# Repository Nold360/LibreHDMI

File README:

# LibreHDMI

The MS9288A is a low-cost, low-power, high performance device, which consists of HDMI Transmitter, three 10-bit video Analog-to-Digital Converters and audio encoder, which can convert VGA or YPbPr signals to HDMI, maximum conversion rate of 165MHz. MS9288A support L/R audio input.MS9288A with embedded MCU and ROM code. 

## Images

### Front

### Back

## Key Features
- Support Sync-on-Green(SOG)
- VGA/YPbPr auto detection
- Double channel 24-bit ADC
- Support I2C slave Interface
- Sample rate is 48KHz
- I2C master interface for DDC control
- Support HDMI 1.3 and DVI1.0
- Integrated HDMI 1.3 TMDS core running at 165MHz
- Support 24-bit color depth and Resolutions up to 1080P@60Hz
- 3.3V and 1.8V power supply

Source: http://en.macrosilicon.com/info.asp?base_id=2&third_id=16

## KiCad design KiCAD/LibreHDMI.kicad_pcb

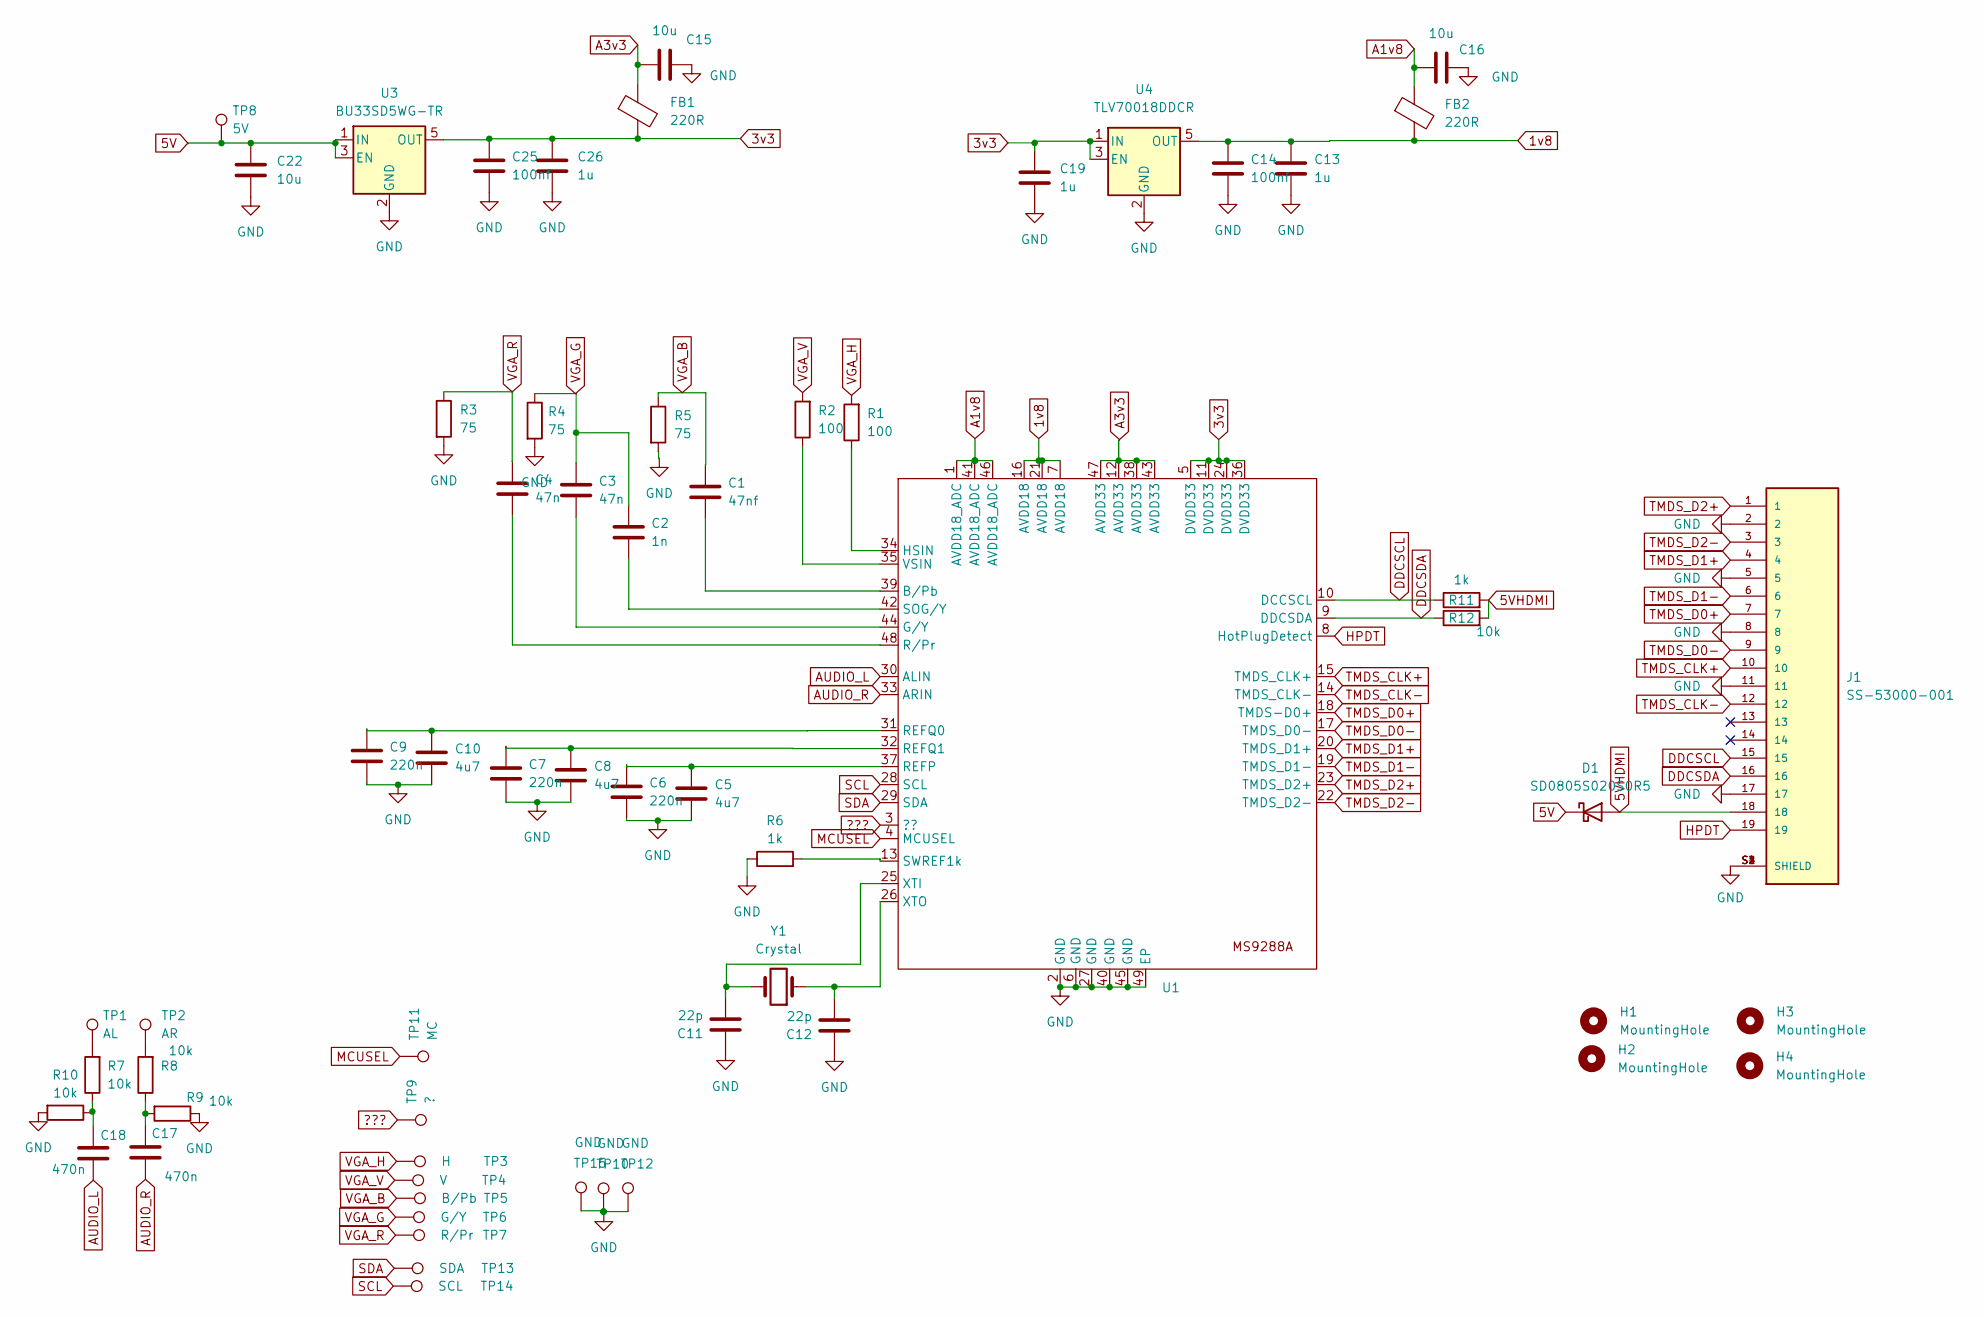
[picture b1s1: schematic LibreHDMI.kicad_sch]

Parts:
C1: 47nf; C_0402_1005Metric
C2: 1n; C_0402_1005Metric
C3, C4: 47n; C_0402_1005Metric
C5, C8, C10: 4u7; C_0402_1005Metric
C6, C7, C9: 220n; C_0402_1005Metric
C11, C12: 22p; C_0402_1005Metric
C13, C19: 1u; C_0402_1005Metric
C14, C25: 100nf; C_0402_1005Metric
C15, C16: 10u; C_0603_1608Metric
C17, C18: 470n; C_0402_1005Metric
C22: 10u; C_0402_1005Metric
C26: 1u; C_0603_1608Metric
D1: SD0805S020S0R5; D_0603_1608Metric
FB1, FB2: 220R; R_0603_1608Metric
H1, H2, H3, H4: MountingHole; MountingHole_2.2mm_M2
J1: SS-53000-001; STEWART_SS-53000-001; PARTREV A0
R1, R2: 100; R_0402_1005Metric
R3, R4, R5: 75; R_0402_1005Metric
R6, R11: 1k; R_0402_1005Metric
R7, R8, R9, R10, R12: 10k; R_0402_1005Metric
TP1: AL; CasPowerPad 2x1
TP2: AR; CasPowerPad 2x1
TP3: H; CasPowerPad 2x1
TP4: V; CasPowerPad 2x1
TP5: B/Pb; CasPowerPad 2x1
TP6: G/Y; CasPowerPad 2x1
TP7: R/Pr; CasPowerPad 2x1
TP8: 5V; CasPowerPad 2x1
TP9: ?; nolds-TestPoint_Pad_D1.0mm
TP10, TP12, TP15: GND; CasPowerPad 2x1
TP11: MC; nolds-TestPoint_Pad_D1.0mm
TP13: SDA; CasPowerPad 2x1
TP14: SCL; CasPowerPad 2x1
U1: QFN-48-1EP_6x6mm_P0.4mm_EP4.2x4.2mm_ThermalVias
U3: BU33SD5WG-TR; SOT-23-5
U4: TLV70018DDCR; SOT-23-5
Y1: Crystal; Crystal_SMD_5032-2Pin_5.0x3.2mm

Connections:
1v8: C13.1, C14.1, FB2.2, U1.7 (AVDD18), U1.16 (AVDD18), U1.21 (AVDD18), U4.5 (OUT)
3v3: C19.1, C25.1, C26.1, FB1.2, U1.5 (DVDD33), U1.11 (DVDD33), U1.24 (DVDD33), U1.36 (DVDD33), U3.5 (OUT), U4.1 (IN), U4.3 (EN)
5V: C22.1, D1.1 (K), TP8.1, U3.1 (IN), U3.3 (EN)
5VHDMI: D1.2 (A), J1.18, R11.2, R12.2
???: TP9.1, U1.3 (??)
A1v8: C16.1, FB2.1, U1.1 (AVDD18_ADC), U1.41 (AVDD18_ADC), U1.46 (AVDD18_ADC)
A3v3: C15.1, FB1.1, U1.12 (AVDD33), U1.38 (AVDD33), U1.43 (AVDD33), U1.47 (AVDD33)
AUDIO_L: C18.2, U1.30 (ALIN)
AUDIO_R: C17.2, U1.33 (ARIN)
DDCSCL: J1.15, R11.1, U1.10 (DCCSCL)
DDCSDA: J1.16, R12.1, U1.9 (DDCSDA)
GND: C5.2, C6.2, C7.2, C8.2, C9.2, C10.2, C11.1, C12.1, C13.2, C14.2, C15.2, C16.2, C19.2, C22.2, C25.2, C26.2, J1.2, J1.5, J1.8, J1.11, J1.17, J1.S1 (SHIELD), J1.S2 (SHIELD), J1.S3 (SHIELD), J1.S4 (SHIELD), R3.2, R4.2, R5.2, R6.1, R9.1, R10.2, TP10.1, TP12.1, TP15.1, U1.2 (GND), U1.6 (GND), U1.27 (GND), U1.40 (GND), U1.45 (GND), U1.49 (EP), U3.2 (GND), U4.2 (GND)
HPDT: J1.19, U1.8 (HotPlugDetect)
MCUSEL: TP11.1, U1.4 (MCUSEL)
unnamed: C17.1, R8.1, R9.2
unnamed: C18.1, R7.1, R10.1
unnamed: R7.2, TP1.1
unnamed: R8.2, TP2.1
unnamed: C1.2, U1.39 (B/Pb)
unnamed: C3.2, U1.44 (G/Y)
unnamed: R1.1, U1.34 (HSIN)
unnamed: C5.1, C6.1, U1.37 (REFP)
unnamed: C9.1, C10.1, U1.31 (REFQ0)
unnamed: C7.1, C8.1, U1.32 (REFQ1)
unnamed: C4.2, U1.48 (R/Pr)
unnamed: C2.2, U1.42 (SOG/Y)
unnamed: R6.2, U1.13 (SWREF1k)
unnamed: R2.1, U1.35 (VSIN)
unnamed: C11.2, U1.25 (XTI), Y1.2
unnamed: C12.2, U1.26 (XTO), Y1.1
SCL: TP14.1, U1.28 (SCL)
SDA: TP13.1, U1.29 (SDA)
TMDS_CLK+: J1.10, U1.15 (TMDS_CLK+)
TMDS_CLK-: J1.12, U1.14 (TMDS_CLK-)
TMDS_D0+: J1.7, U1.18 (TMDS-D0+)
TMDS_D0-: J1.9, U1.17 (TMDS_D0-)
TMDS_D1+: J1.4, U1.20 (TMDS_D1+)
TMDS_D1-: J1.6, U1.19 (TMDS_D1-)
TMDS_D2+: J1.1, U1.23 (TMDS_D2+)
TMDS_D2-: J1.3, U1.22 (TMDS_D2-)
VGA_B: C1.1, R5.1, TP5.1
VGA_G: C2.1, C3.1, R4.1, TP6.1
VGA_H: R1.2, TP3.1
VGA_R: C4.1, R3.1, TP7.1
VGA_V: R2.2, TP4.1

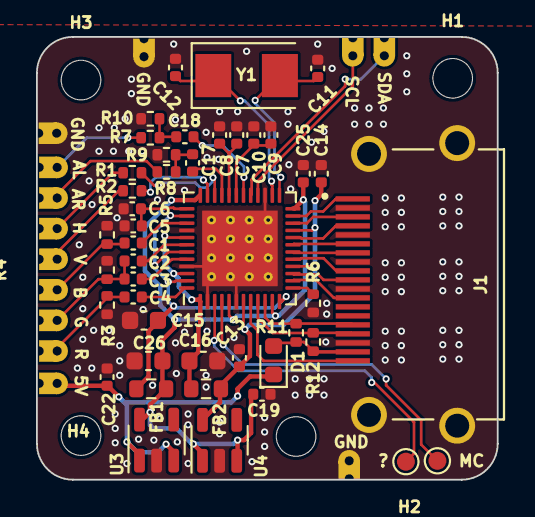
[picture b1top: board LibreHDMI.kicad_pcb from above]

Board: 2 copper layers, 25.6 x 24.6 mm, 61 parts (0 on the bottom side), 45 nets.

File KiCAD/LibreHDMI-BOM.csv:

"Reference","Value","Datasheet","Footprint","Qty","DNP"
"C1","47nf","~","Capacitor_SMD:C_0402_1005Metric","1",""
"C2","1n","~","Capacitor_SMD:C_0402_1005Metric","1",""
"C3,C4","47n","~","Capacitor_SMD:C_0402_1005Metric","2",""
"C5,C8,C10","4u7","~","Capacitor_SMD:C_0402_1005Metric","3",""
"C6,C7,C9","220n","~","Capacitor_SMD:C_0402_1005Metric","3",""
"C11,C12","22p","~","Capacitor_SMD:C_0402_1005Metric","2",""
"C13,C19,C26","1u","~","-- mixed values --","3",""
"C14,C25","100nf","~","Capacitor_SMD:C_0402_1005Metric","2",""
"C15,C16,C22","10u","~","-- mixed values --","3",""
"C17,C18","470n","~","Capacitor_SMD:C_0402_1005Metric","2",""
"D1","SD0805S020S0R5","~","Diode_SMD:D_0603_1608Metric","1",""
"FB1,FB2","220R","~","Resistor_SMD:R_0603_1608Metric","2",""
"H1,H2,H3,H4","MountingHole","~","MountingHole:MountingHole_2.2mm_M2","4",""
"J1","SS-53000-001","","000-symbols-footprints:STEWART_SS-53000-001","1",""
"R1,R2","100","~","Resistor_SMD:R_0402_1005Metric","2",""
"R3,R4,R5","75","~","Resistor_SMD:R_0402_1005Metric","3",""
"R6,R11","1k","~","Resistor_SMD:R_0402_1005Metric","2",""
"R7,R8,R9,R10,R12","10k","~","Resistor_SMD:R_0402_1005Metric","5",""
"TP1","AL","~","000-nold-customs:CasPowerPad 2x1","1",""
"TP2","AR","~","000-nold-customs:CasPowerPad 2x1","1",""
"TP3","H","~","000-nold-customs:CasPowerPad 2x1","1",""
"TP4","V","~","000-nold-customs:CasPowerPad 2x1","1",""
"TP5","B/Pb","~","000-nold-customs:CasPowerPad 2x1","1",""
"TP6","G/Y","~","000-nold-customs:CasPowerPad 2x1","1",""
"TP7","R/Pr","~","000-nold-customs:CasPowerPad 2x1","1",""
"TP8","5V","~","000-nold-customs:CasPowerPad 2x1","1",""
"TP9","?","~","000-nold-customs:nolds-TestPoint_Pad_D1.0mm","1",""
"TP10,TP12,TP15","GND","~","000-nold-customs:CasPowerPad 2x1","3",""
"TP11","MC","~","000-nold-customs:nolds-TestPoint_Pad_D1.0mm","1",""
"TP13","SDA","~","000-nold-customs:CasPowerPad 2x1","1",""
"TP14","SCL","~","000-nold-customs:CasPowerPad 2x1","1",""
"U1","~","","Package_DFN_QFN:QFN-48-1EP_6x6mm_P0.4mm_EP4.2x4.2mm_ThermalVias","1",""
"U3","BU33SD5WG-TR","http://www.ti.com/lit/ds/symlink/tlv700.pdf","Package_TO_SOT_SMD:SOT-23-5","1",""
"U4","TLV70018DDCR","http://www.ti.com/lit/ds/symlink/tlv700.pdf","Package_TO_SOT_SMD:SOT-23-5","1",""
"Y1","Crystal","~","Crystal:Crystal_SMD_5032-2Pin_5.0x3.2mm","1",""

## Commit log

2024-12-28 init
2024-12-28 fix readme
